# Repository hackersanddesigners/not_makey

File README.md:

# not_makey

This repository describes how to manufacture a shield for the ESP32, and the code to program pins as resistive touch sensors that each send strings to a laptop over Bluetooth. It is programmed to send letters that correspond with PJ machine keycodes used in e.g. this workshop https://github.com/hackersanddesigners/interfacial-workout-23

On the board you can see which pins are connected to which letter. Pins without a letter are free to use for something else (e.g. sensors, LEDs), additional code can be written inside the sketch. 

To send a letter to the laptop: 
- connect laptop to bluetooth device "NOT_MAKEY" (esp and shield should be connected to a power source)
- open a textpad on the laptop
- touch a probe connected to one of the letter pins, and a probe connected to GND to send a letter via Bluetooth

## acknowledgments

* Joylab's Jay Silver & Erik Rosenbaum's *MakeyMakey board* [https://github.com/sparkfun/MaKeyMaKey](https://github.com/sparkfun/MaKeyMaKey)
* Manualbl's [repository on using ESP32 as Bluetooth Keyboard](https://gist.github.com/manuelbl/66f059effc8a7be148adb1f104666467)
* Jack Christensen's [moving average library](https://github.com/JChristensen/movingAvg)

# v2 via Aisler board house

## bill of materials v.2 

* an ESP32 WROOM devkit, e.g. [this one from Espressif](https://www.espressif.com/en/products/modules/esp32) €14,49 at [Reichelt](https://www.reichelt.nl/nl/nl/entwicklungsboard-esp32-wroom-32e-esp32devkitc32e-p341303.html?&trstct=pos_1&nbc=1)
* mini usb programming cable e.g. [this one at kiwi](https://www.kiwi-electronics.com/nl/microusb-kabel-usb-a-naar-micro-b-15cm-3240?search=usb-A%20naar%20micro-b) €1,25
* 4x single row break-away female header strips (you need 4x a single row strips of 15 positions) e.g. [this one](https://www.reichelt.nl/nl/nl/vrouwelijke-connector-2-54mm-1x20-scheidbaar-vertind-fis-bl1-20-z-p283794.html?&nbc=1) at Reichelt €1,22 each
* 14x 22Mohm resistors e.g. [this one](https://nl.farnell.com/yageo/hhv-25jt-52-22m/res-22m-5-250mw-axial-metal-film/dp/1779371?st=22m%20ohm%20resistor) at Farnell €0,07 each. These can be hard to find in DIY shops you might need to look at Farnell, Mouser, or get some from China :(
* 14x (or more) MM dupont jumper wires to access the pins
* alligator clips to connect connective stuff to the board. 

## schematic

The schematic is the same

## board design

The silkscreen is a bit more elaborate so you can see what character corresponds with which pin in the code.

## board house link

[https://aisler.net/p/JORJIJIP](https://aisler.net/p/JORJIJIP)

## soldering

For this board, you'll need to have the inner 2 connector rows facing down to connect to the ESP32 

The outer two connector rows are facing outward, to give access to the pins via jumper wires

## programming the ESP

[Arduino code](./arduino/esp32_ble_makey_14probes/esp32_ble_makey_14probes.ino)

This program lets an ESP32 act as a keyboard connected via Bluetooth.
When a button attached to the ESP32 is pressed, it will generate the key strokes

In order to receive the message, add the ESP32 as a Bluetooth keyboard of your computer or mobile phone:

  1. Go to your computers/phones settings
  2. Ensure Bluetooth is turned on
  3. Scan for Bluetooth devices
  4. Connect to the device called "NOT_MAKEY" (you can change this name in the code)
  5. Open an empty document in a text editor
  6. Press the buttons attached to the ESP32 to generate different letters
 
If the probes don't respond too well you can troubleshoot and calibrate with simple code using the moving average filter and printing it to the serial. 

[Moving AVG testcode](./arduino/esp32_movingAVG_analogread/esp32_movingAVG_analogread.ino)

### Select the board

* Open Arduino preferences pane and paste the following URL in the box "Additional Boards Manager URLs"

```https://espressif.github.io/arduino-esp32/package_esp32_index.json```

* Open the Boards Manager. Go to Tools > Board > Boards Manager… 
* Search for "ESP32" and press install for "ESP32 by Espressif Systems"
* Go to > Tools > Board > ESP32 Arduino > ESP32 Devkit
* If it doesnt' show up, restart the Arduino IDE

### Compile the code to check libs are working

Compile to check if you have all the libraries. If not, check the console for troubleshooting. If necessary, install these: 

* MovingAVG library by Jack Christensen (via library manager)
* [BLE library](https://reference.arduino.cc/reference/en/libraries/esp32-ble-arduino/) (via library manger)
* [ESP32 libraries](https://github.com/espressif/arduino-esp32/tree/master/libraries) (I believe these are installed automaticallly with the ESP32 board files, so shouldn't give any problems).

### Testing 

* Connect the board to the computer with a USB data cable and upload the code
* Connect the ESP to the shield, taking care the orientation is correct. 
* Connect probes, e.g. jumper wires to one or two pins with a letter next to it
* Connect a laptop to the bluetooth device called "NOT_MAKEY" (name can be changed in line 63 in the code)
* Open a notepad on the connected laptop
* Test by touching a probe with one finger, while touching the 3V3 with the other finger. The principle is the same as makey makey, but here the resistors are connected as a pull-up resistor (keeps the signal high until a change is registered), so you touch one of the pins AND 3V3 (instead of one of the pins and GND as you would on the makey makey).

# Previous versions

## v1 via fablab

## tools

* Roland Modela MDX-20 with MODS for pcb production installed (only works in Chrome) modsproject.org

Note that this process doesn't require Gerber files, instead you need a 1000 DPI black and monochrome images of the bottom of the board, and separate files with holes and the board outline).

* Soldering station, solder, clippers

## bill of materials v.1 

* an ESP32 WROOM devkit, e.g. [this one from Espressif](https://www.espressif.com/en/products/modules/esp32) €14,49 at [Reichelt](https://www.reichelt.nl/nl/nl/entwicklungsboard-esp32-wroom-32e-esp32devkitc32e-p341303.html?&trstct=pos_1&nbc=1)
* mini usb programming cable e.g. [this one at kiwi](https://www.kiwi-electronics.com/nl/microusb-kabel-usb-a-naar-micro-b-15cm-3240?search=usb-A%20naar%20micro-b) €1,25
* 2x single row break-away female header strips (you need 2x a single row strips of 15 positions) e.g. [this one](https://www.reichelt.nl/nl/nl/vrouwelijke-connector-2-54mm-1x20-scheidbaar-vertind-fis-bl1-20-z-p283794.html?&nbc=1) at Reichelt €1,22 each
* 14x 22Mohm resistors e.g. [this one](https://nl.farnell.com/yageo/hhv-25jt-52-22m/res-22m-5-250mw-axial-metal-film/dp/1779371?st=22m%20ohm%20resistor) at Farnell €0,07 each. These can be hard to find in DIY shops you might need to look at Farnell, Mouser, or get some from China :(
* 14 or more Alligator clips to connect your DIY buttons to the board

*Break-away header strip*

## software & dependencies

* Arduino IDE: [www.arduino.cc](www.arduino.cc)
	* Install the board with the board manager: 
		* *esp32* by espressif
		* select board > ESP Arduino > ESP 32 Dev Module  
	* Install the following libraries: 
		* *movingAVG.h* by Jack Christensen
		* the other libs included in the code don't seem to need an install (perhaps come with ESP32 board definitions? > check)
* Eagle (if you want to edit or redesign the board)
* GIMP or photoshop (if you want to edit the milling files directly)

## manufacturing the shield

### prototyping setup

### schematic v.1

### board v.1 

### fabrication files for Roland modela MDX-20

####**Exporting the design from Eagle**

* exported as PNG images from Eagle at 1000 dpi in monochrome
	* MILLING - traces - exported layers: bottom, pads, via's
	* DRILLING - holes and board outline - exported layers: vias & 

####**Editing the images**

* resize images to 50% in photoshop (something happens in the export from eagle)

#####*Bottom_v1.png*

* deleted little bits and text with bucket tool
* added new text (that is not in mirror image :D) 

#####*Holes_v1.png* 

* Deleted the big 4 holes on top and bottom of the board, they're not needed but came with the footprint

#####*Dimension_v1.png*

* manually drew a rectangle larger than the board outline to make sure the board dimension is visible in the image (otherwise it's right at the edge)

### milling the PCB

* Mill the [bottom.png file](./fabrication/bottom.png)
* Drill holes [cut.png file](./fabrication/cut.png)
* Mill outline [outline.png file](./fabrication/?????)
* Wash
* Test connections
* Make corrections

### soldering

Solder resistors & connectors as per board layout

## wishes based on v.1

* pads are very small, not handy. Add second row of connector pins instead? (saves space)
* bigger footprint for resistors (min .8mm drill holes, thicked pads)

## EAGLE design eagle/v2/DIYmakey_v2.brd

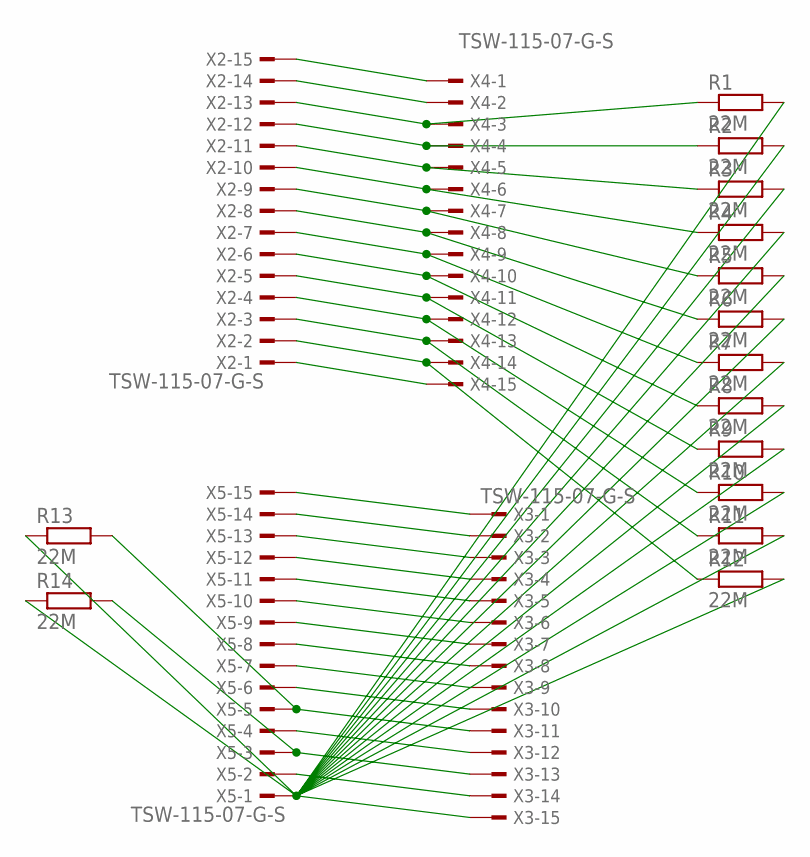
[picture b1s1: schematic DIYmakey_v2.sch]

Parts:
R1, R2, R3, R4, R5, R6, R7, R8, R9, R10, R11, R12, R13, R14: 22M; 0207/7
X2, X3, X4, X5: TSW-115-07-G-S; TSW-115-XX-G-S

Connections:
unnamed: X2.15, X4.1
unnamed: X2.14, X4.2
unnamed: R1.1, X2.13, X4.3
unnamed: R2.1, X2.12, X4.4
unnamed: R3.1, X2.11, X4.5
unnamed: R4.1, X2.10, X4.6
unnamed: R5.1, X2.9, X4.7
unnamed: R6.1, X2.8, X4.8
unnamed: R7.1, X2.7, X4.9
unnamed: R8.1, X2.6, X4.10
unnamed: R9.1, X2.5, X4.11
unnamed: R10.1, X2.4, X4.12
unnamed: R11.1, X2.3, X4.13
unnamed: R12.1, X2.2, X4.14
unnamed: X2.1, X4.15
unnamed: X3.1, X5.15
unnamed: X3.2, X5.14
unnamed: X3.3, X5.13
unnamed: X3.4, X5.12
unnamed: X3.5, X5.11
unnamed: X3.6, X5.10
unnamed: X3.7, X5.9
unnamed: X3.8, X5.8
unnamed: X3.9, X5.7
unnamed: X3.10, X5.6
unnamed: R13.2, X3.11, X5.5
unnamed: X3.12, X5.4
unnamed: R14.2, X3.13, X5.3
unnamed: X3.14, X5.2
unnamed: R1.2, R2.2, R3.2, R4.2, R5.2, R6.2, R7.2, R8.2, R9.2, R10.2, R11.2, R12.2, R13.1, R14.1, X3.15, X5.1

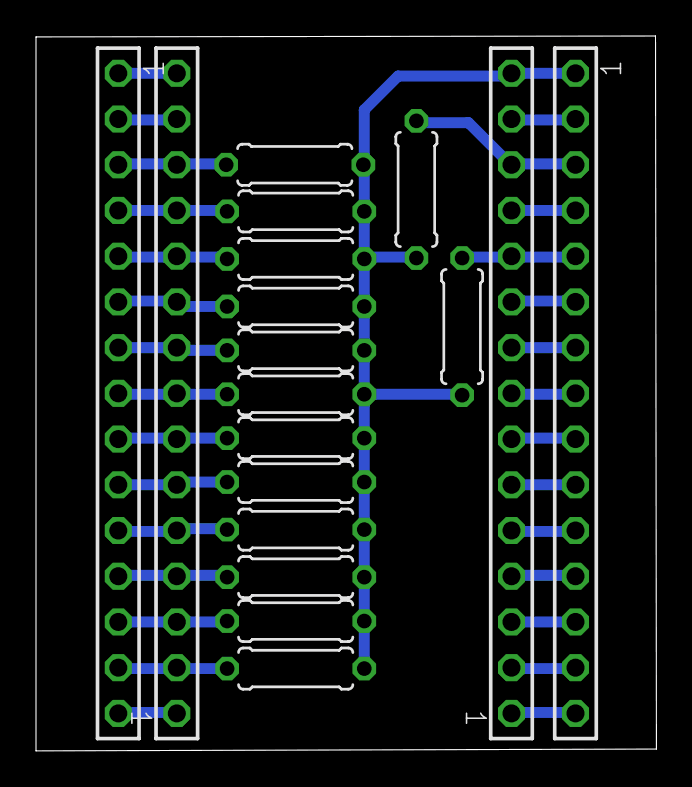
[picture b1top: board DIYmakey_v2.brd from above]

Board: 2 copper layers, 34.5 x 39.7 mm, 18 parts (0 on the bottom side), 30 nets.

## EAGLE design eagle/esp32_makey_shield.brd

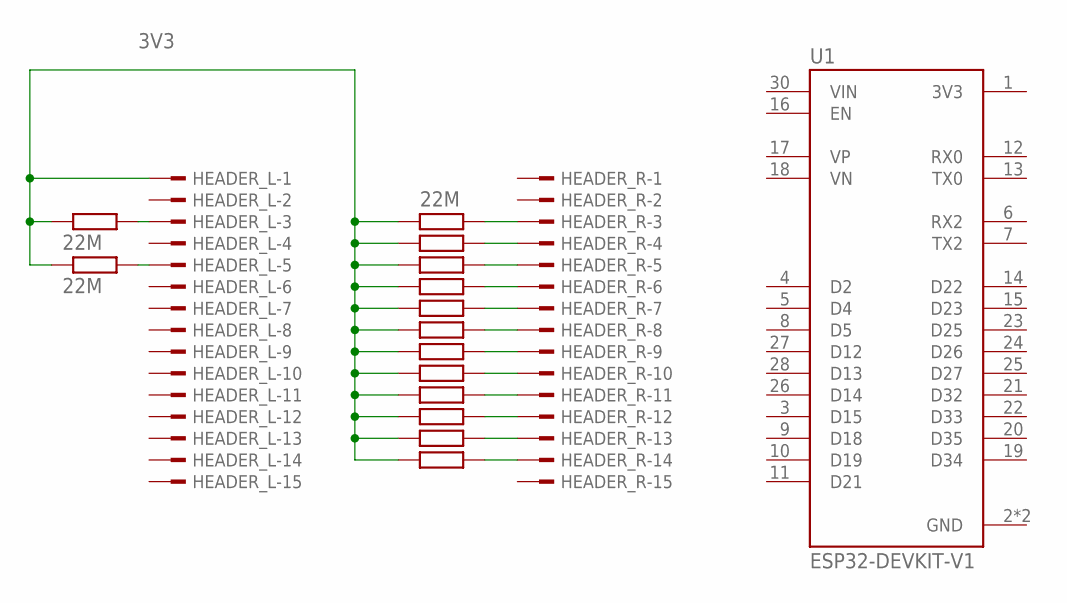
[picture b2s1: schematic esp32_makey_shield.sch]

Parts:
HEADER_L: TSW-115-07-G-S; TSW-115-XX-G-S
HEADER_R: TSW-115-07-G-S; TSW-115-XX-G-S
R1, R2, R3, R4, R5, R6, R7, R8, R9, R10, R11, R12, R13, R14: 22M; 0204/7
U1: ESP32-DEVKIT-V1; MODULE_ESP32_DEVKIT_V1

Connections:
3V3: HEADER_L.1, R1.1, R2.1, R3.1, R4.1, R5.1, R6.1, R7.1, R8.1, R9.1, R10.1, R11.1, R12.1, R13.1, R14.1
GND: U1.2 (GND), U1.29 (GND)
unnamed: HEADER_L.3, R13.2
unnamed: HEADER_L.5, R14.2
unnamed: HEADER_R.3, R1.2
unnamed: HEADER_R.4, R2.2
unnamed: HEADER_R.5, R3.2
unnamed: HEADER_R.6, R4.2
unnamed: HEADER_R.7, R5.2
unnamed: HEADER_R.8, R6.2
unnamed: HEADER_R.9, R7.2
unnamed: HEADER_R.10, R8.2
unnamed: HEADER_R.11, R9.2
unnamed: HEADER_R.12, R10.2
unnamed: HEADER_R.13, R11.2
unnamed: HEADER_R.14, R12.2

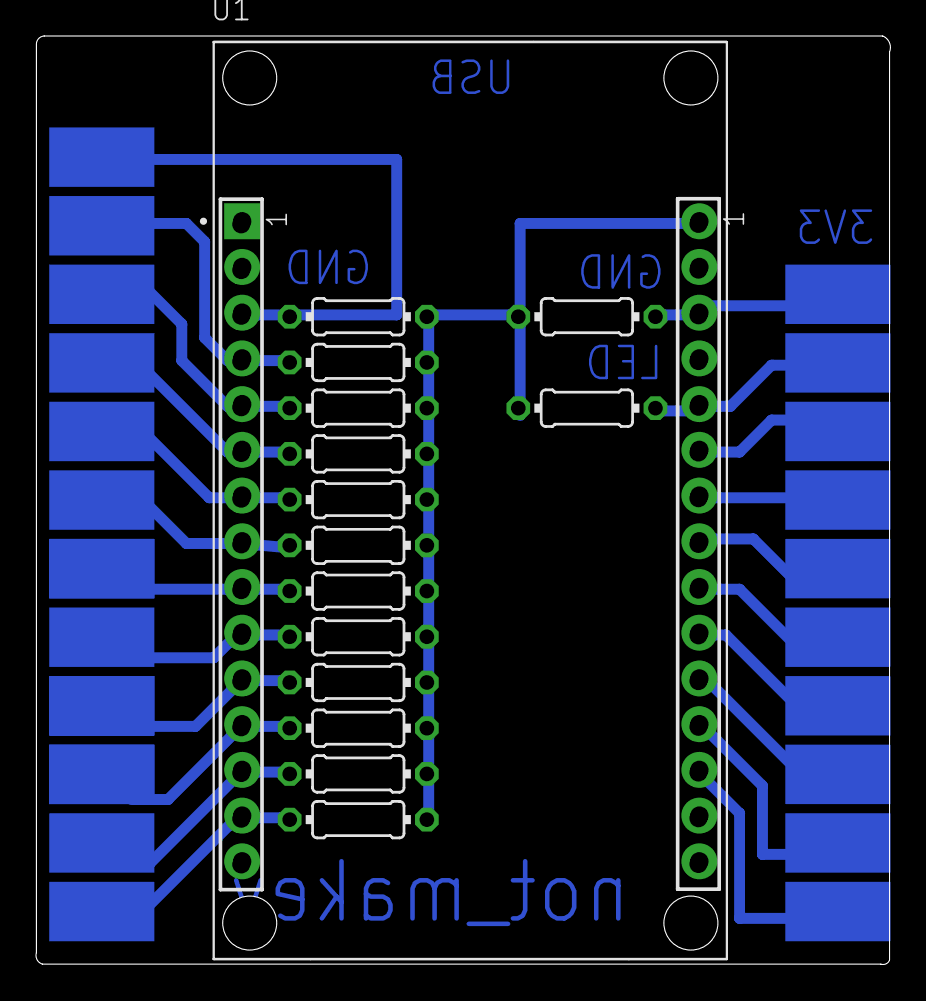
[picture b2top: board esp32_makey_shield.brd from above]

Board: 2 copper layers, 47.5 x 51.6 mm, 17 parts (0 on the bottom side), 16 nets.

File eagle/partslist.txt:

Partlist

Exported from esp32_makey_shield.brd at 27/01/2023 16:15

EAGLE Version 9.6.2 Copyright (c) 1988-2020 Autodesk, Inc.

Assembly variant: 

Part        Value           Package                Library         Position (mil)        Orientation		Description
	

ADCPINS     TSW-115-07-G-S  TSW-115-XX-G-S         con-samtec      (460 918)             R90			15 pin female single row header 2.54 pitch      	
MOSTLYEMPTY TSW-115-07-G-S  TSW-115-XX-G-S         con-samtec      (1460 919)            R90			15 pin female single row header 2.54 pitch
R1          22M             0204/7                 rcl             (716 1416)            R180			22M ohm resistor (throughhole)
R2          22M             0204/7                 rcl             (716 1316)            R180			22M ohm resistor (throughhole)
R3          22M             0204/7                 rcl             (716 1216)            R180			22M ohm resistor (throughhole)
R4          22M             0204/7                 rcl             (716 1116)            R180			22M ohm resistor (throughhole)
R5          22M             0204/7                 rcl             (716 1016)            R180			22M ohm resistor (throughhole)
R6          22M             0204/7                 rcl             (716 916)             R180			22M ohm resistor (throughhole)
R7          22M             0204/7                 rcl             (716 816)             R180			22M ohm resistor (throughhole)
R8          22M             0204/7                 rcl             (716 716)             R180			22M ohm resistor (throughhole)
R9          22M             0204/7                 rcl             (716 616)             R180			22M ohm resistor (throughhole)
R10         22M             0204/7                 rcl             (716 516)             R180			22M ohm resistor (throughhole)
R11         22M             0204/7                 rcl             (716 416)             R180			22M ohm resistor (throughhole)
R12         22M             0204/7                 rcl             (716 316)             R180			22M ohm resistor (throughhole)
R13         22M             0204/7                 rcl             (1216 1416)           R0			22M ohm resistor (throughhole)
R14         22M             0204/7                 rcl             (1216 1216)           R0			22M ohm resistor (throughhole)
U1          ESP32-DEVKIT-V1 MODULE_ESP32_DEVKIT_V1 ESP32-DEVKIT-V1 (962 1014)            R0			ESP32-WROOM devkit (e.g. espressif)

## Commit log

2023-01-28 add files
2023-05-31 add v2 ready for aisler fabrication
2023-06-19 add v2
2023-07-12 add code and soldering documentation
2023-07-12 add workdoc for soldering in case mistakes
2023-07-21 fix GND probe update wiring
2023-08-29 update test name device
    add
